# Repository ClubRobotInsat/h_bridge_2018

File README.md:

# h_bridge_2018
The H bridge PCB we use to power and control our DC motors

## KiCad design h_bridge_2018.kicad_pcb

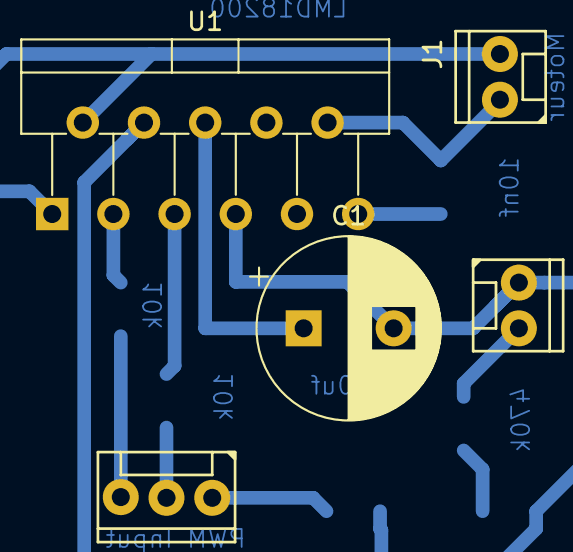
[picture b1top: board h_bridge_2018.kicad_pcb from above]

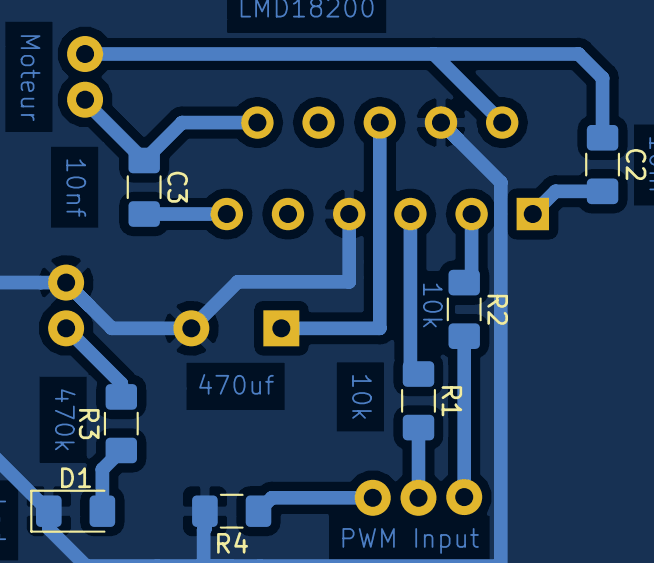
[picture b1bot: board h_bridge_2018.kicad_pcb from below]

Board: 2 copper layers, 12 parts (7 on the bottom side), 13 nets.

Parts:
C1: 470uF; CP_Radial_D10.0mm_P5.00mm
C2, C3: 10nF; C_1206_3216Metric_Pad1.42x1.75mm_HandSolder
D1: LED_3MM ROUGE; LED_1206_3216Metric_Pad1.42x1.75mm_HandSolder
J1: U$4; HE14-2-straight
J2: Alim puissance; HE14-2-straight
J7: PWM input; HE14-3-straight
R1, R2: 10k; R_1206_3216Metric_Pad1.42x1.75mm_HandSolder
R3: 470; R_1206_3216Metric_Pad1.42x1.75mm_HandSolder
R4: 0; R_1206_3216Metric_Pad1.42x1.75mm_HandSolder
U1: LMD18200; TO-220-11_P3.4x5.08mm_StaggerOdd_Lead4.85mm_Vertical

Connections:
/VS: J2.2, R3.2
GNDPWR: C1.2, D1.1, J2.1, R4.2, U1.4, U1.7
unnamed: C1.1, U1.6
unnamed: C2.1, J1.2, U1.2
unnamed: C2.2, U1.1
unnamed: C3.1, J1.1, U1.10
unnamed: C3.2, U1.11
unnamed: D1.2, R3.1
unnamed: J7.1, R4.1
unnamed: J7.2, R1.2
unnamed: J7.3, R2.2
unnamed: R1.1, U1.5
unnamed: R2.1, U1.3

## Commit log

2018-12-20 added sources
2019-02-21 Premier PCB
2019-03-28 h_bridge modified version
